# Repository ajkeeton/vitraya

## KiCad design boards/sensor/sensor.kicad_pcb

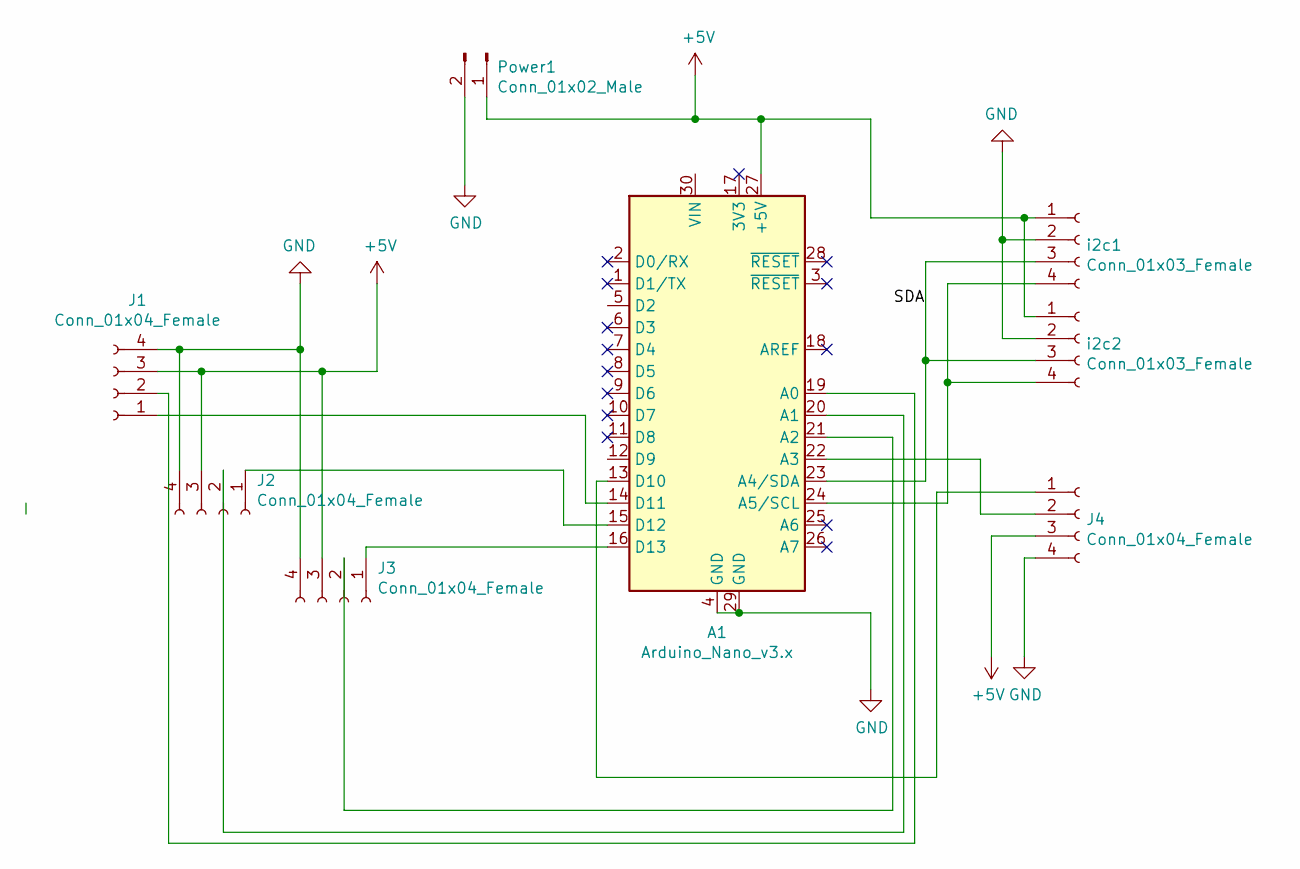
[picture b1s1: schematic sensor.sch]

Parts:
A1: Arduino_Nano_v3.x; Arduino_Nano
J1, J2, J3, J4: Conn_01x04_Female; PinHeader_1x04_P2.54mm_Vertical
Power1: Conn_01x02_Male; PinHeader_1x02_P2.54mm_Vertical
i2c1, i2c2: Conn_01x03_Female; PinHeader_1x04_P2.54mm_Vertical

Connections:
+5V: A1.27 (+5V), J1.3, J2.3, J3.3, J4.3, Power1.1, i2c1.1, i2c2.1
GND: A1.4 (GND), A1.29 (GND), J1.4, J2.4, J3.4, J4.4, Power1.2, i2c1.2, i2c2.2
unnamed: A1.13 (D10), J4.1
unnamed: A1.14 (D11), J1.1
unnamed: A1.15 (D12), J2.1
unnamed: A1.16 (D13), J3.1
unnamed: A1.19 (A0), J1.2
unnamed: A1.20 (A1), J2.2
unnamed: A1.21 (A2), J3.2
unnamed: A1.22 (A3), J4.2
unnamed: A1.23 (A4/SDA), i2c1.3, i2c2.3
unnamed: A1.24 (A5/SCL), i2c1.4, i2c2.4

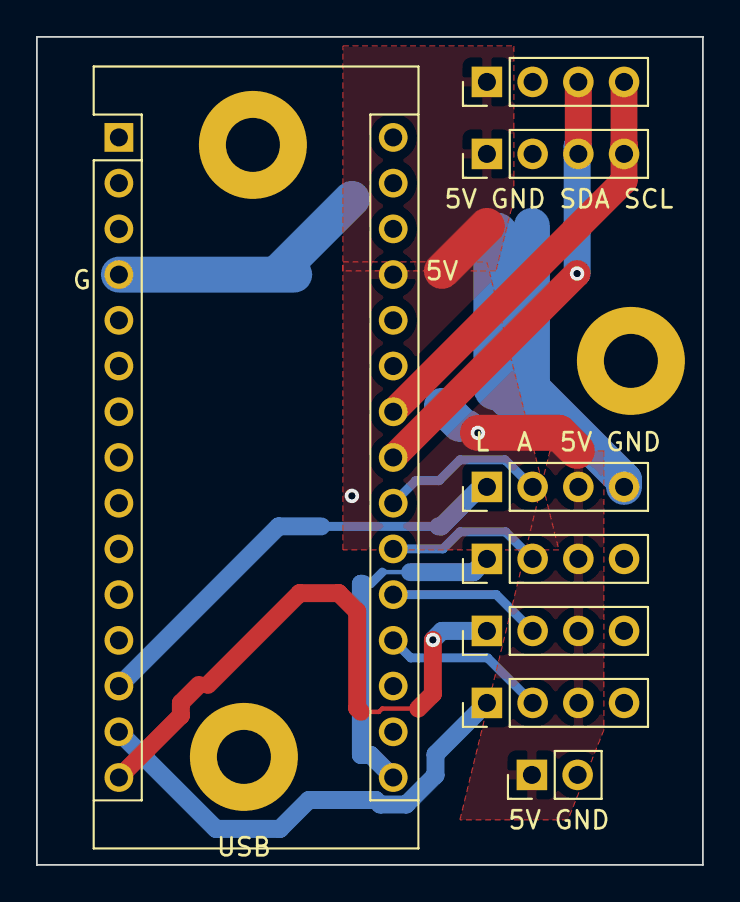
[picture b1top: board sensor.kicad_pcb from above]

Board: 2 copper layers, 37.0 x 46.0 mm, 8 parts (0 on the bottom side), 12 nets.

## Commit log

2021-08-01 First steps
2021-08-06 First stab at the Arduino code
2021-08-06 More fleshy bits
2021-08-15 Midi'ing, refactored, more Arduino flesh
2021-08-15 Better sensor interface
2021-08-15 Adding cmds.py
2021-08-15 Cleaning up server
2021-08-15 Tweaking proto
2021-08-15 Cleaning up midi/knob code
2021-11-12 First pass with controller pcb
2021-11-19 Submitted board
2021-12-17 Updates for new board
